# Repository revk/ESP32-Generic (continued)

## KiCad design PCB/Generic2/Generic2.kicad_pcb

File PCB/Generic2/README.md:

# Generic2

## Trademark

This is an open source project, but bear in mind you cannot sell boards bearing the Andrews & Arnold Ltd name, the A&A logo, the registered trademark AJK logo, or the GS1 allocated EANs assigned to Andrews & Arnold Ltd.

## PCB Designs

These files are for use with [KiCAD](https://www.kicad.org).

- [Generic2](Generic2.kicad_pro)
## 3D

3D case designs are normally automatically created from the PCB so as to ensure correct details and placement of apertures, etc.

- [Generic2](Generic2.stl)

## Images

---

*Auto generated README.md 2025-08-25T14:29:06*

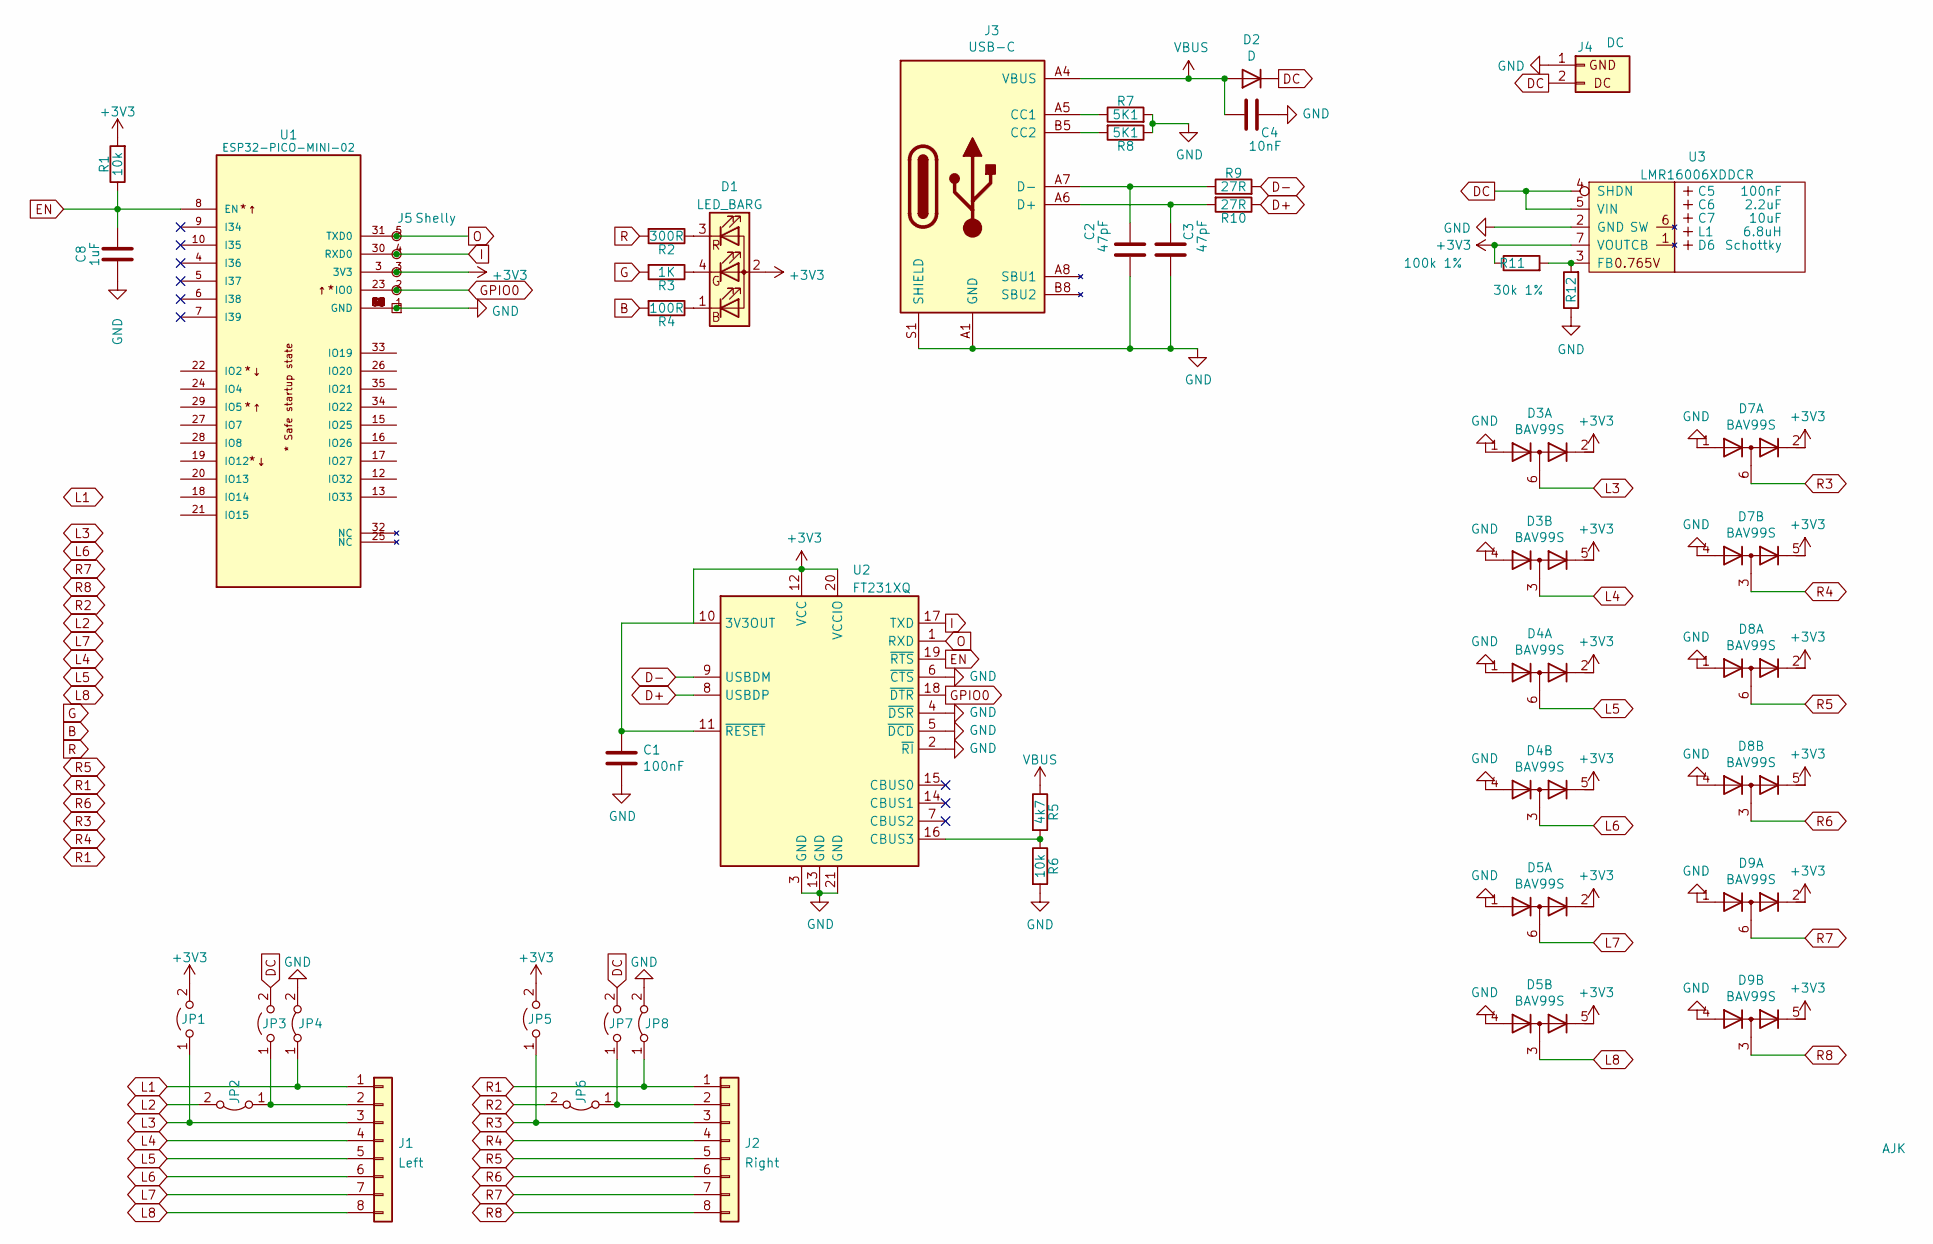
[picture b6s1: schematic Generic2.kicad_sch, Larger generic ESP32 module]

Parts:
C1: 100nF; C_0603
C2, C3: 47pF; C_0603
C4: 10nF; C_0603
C5: 100nF; C_0603_; MPN C30926
C6: 2.2uF; C_0805_; MPN C19110
C7: 10uF; C_0805_; MPN C17024
C8: 1uF; C_0603
D1: LED_BARG; MHS190RGBCT; MPN C409798
D2: D; D_1206_3216Metric
D3, D4, D5, D7, D8, D9: BAV99S; SOT-363_SC-70-6; Part No BAV99S
D6: Schottky; D_1206_; MPN C143805
J1: Left; PTSM-HH-8-RA
J2: Right; PTSM-HH-8-RA
J3: USB-C; USC16-TR; Part No CSP-USC16-TR
J4: DC
J5: Shelly
JP1, JP5: L3; Pad_1206_0805_Open
JP2, JP6: L2; Pad_1206_0805_Bridged
JP3, JP7: L2; Pad_1206_0805_Open
JP4, JP8: L1; Pad_1206_0805_Bridged
L1: 6.8uH; L_4x4_; MPN C354575
Logo1: AJK
R1, R6: 10k; R_0603
R2: 300R; R_0603; Part No 0603-680R
R3: 1K; R_0603; Part No 0603-2K
R4: 100R; R_0603; Part No 0603-220R
R5: 4k7; R_0603
R7, R8: 5K1; R_0603
R9, R10: 27R; R_0603
R11: 100k 1%; R_0603; MPN C14675
R12: 30k 1%; R_0603; MPN C100001
U1: ESP32-PICO-MINI-02; PARTREV v1.0
U2: FT231XQ; QFN-20-1EP_4x4mm_P0.5mm_EP2.5x2.5mm
U3: LMR16006XDDCR; SOT-23-Thin-6-Reg; Part No LMR16006XDDCR

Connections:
+3V3: C1.1, D1.2 (A), D3.2 (K2), D3.5 (K4), D4.2 (K2), D4.5 (K4), D5.2 (K2), D5.5 (K4), D7.2 (K2), D7.5 (K4), D8.2 (K2), D8.5 (K4), D9.2 (K2), D9.5 (K4), J5.3 (3V3), JP1.2 (B), JP5.2 (B), R1.2, R11.1, U1.3 (3V3), U2.10 (3V3OUT), U2.11 (~RESET), U2.12 (VCC), U2.20 (VCCIO), U3.7 (VOUT)
B: R4.2
D+: R10.1, U2.8 (USBDP)
D-: R9.2, U2.9 (USBDM)
DC: D2.1 (K), J4.2 (DC), JP3.2 (B), JP7.2 (B), U3.4 (SHDN), U3.5 (VIN)
EN: C8.2, R1.1, U1.8 (EN), U2.19 (~RTS)
G: R3.2
GND: C1.2, C2.2, C3.2, C4.1, C8.1, D3.1 (A1), D3.4 (A3), D4.1 (A1), D4.4 (A3), D5.1 (A1), D5.4 (A3), D7.1 (A1), D7.4 (A3), D8.1 (A1), D8.4 (A3), D9.1 (A1), D9.4 (A3), J3.A1 (GND), J3.A12 (GND), J3.B1 (GND), J3.B12 (GND), J3.S1 (SHIELD), J4.1 (GND), J5.1 (GND), JP4.2 (B), JP8.2 (B), R6.2, R7.2, R8.1, R12.1, U1.1 (GND), U1.2 (GND), U1.11 (GND), U1.14 (GND), U1.36 (GND), U1.37 (GND), U1.38 (GND), U1.39 (GND), U1.40 (GND), U1.41 (GND), U1.42 (GND), U1.43 (GND), U1.44 (GND), U1.45 (GND), U1.46 (GND), U1.47 (GND), U1.48 (GND), U1.49 (GND), U1.50 (GND), U1.51 (GND), U1.52 (GND), U1.53 (GND), U2.2 (~RI), U2.3 (GND), U2.4 (~DSR), U2.5 (~DCD), U2.6 (~CTS), U2.13 (GND), U2.21 (GND), U3.2 (GND)
GPIO0: J5.2 (0), U1.23 (IO0), U2.18 (~DTR)
I: J5.4 (Rx), U1.30 (RXD0), U2.17 (TXD)
L1: J1.1, JP4.1 (A)
L2: JP2.2 (B)
L3: D3.6 (K3A4), J1.3, JP1.1 (A)
L4: D3.3 (K1A2), J1.4
L5: D4.6 (K3A4), J1.5
L6: D4.3 (K1A2), J1.6
L7: D5.6 (K3A4), J1.7
L8: D5.3 (K1A2), J1.8
unnamed: C2.1, J3.A7 (D-), J3.B7 (D-), R9.1
unnamed: C3.1, J3.A6 (D+), J3.B6 (D+), R10.2
unnamed: D1.1 (BK), R4.1
unnamed: D1.4 (GK), R3.1
unnamed: D1.3 (RK), R2.1
unnamed: J1.2, JP2.1 (A), JP3.1 (A)
unnamed: J2.2, JP6.1 (A), JP7.1 (A)
unnamed: J3.A5 (CC1), R7.1
unnamed: J3.B5 (CC2), R8.2
unnamed: R5.2, R6.1, U2.16 (CBUS3)
unnamed: R11.2, R12.2, U3.3 (FB)
O: J5.5 (Tx), U1.31 (TXD0), U2.1 (RXD)
R: R2.2
R1: J2.1, JP8.1 (A)
R2: JP6.2 (B)
R3: D7.6 (K3A4), J2.3, JP5.1 (A)
R4: D7.3 (K1A2), J2.4
R5: D8.6 (K3A4), J2.5
R6: D8.3 (K1A2), J2.6
R7: D9.6 (K3A4), J2.7
R8: D9.3 (K1A2), J2.8
VBUS: C4.2, D2.2 (A), J3.A4 (VBUS), J3.A9 (VBUS), J3.B4 (VBUS), J3.B9 (VBUS), R5.1

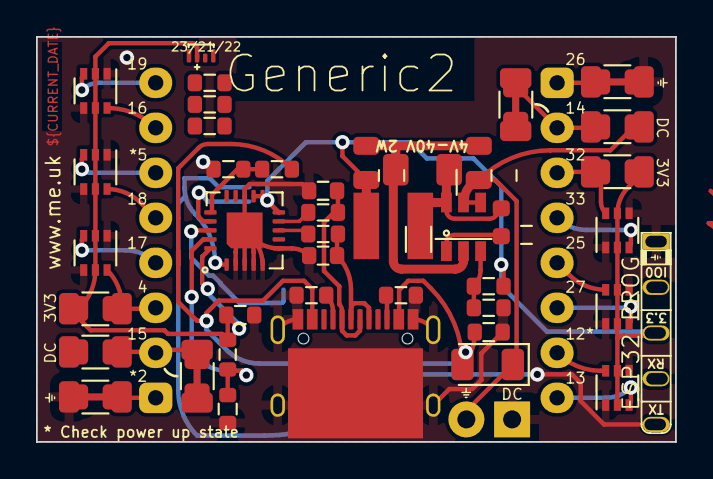
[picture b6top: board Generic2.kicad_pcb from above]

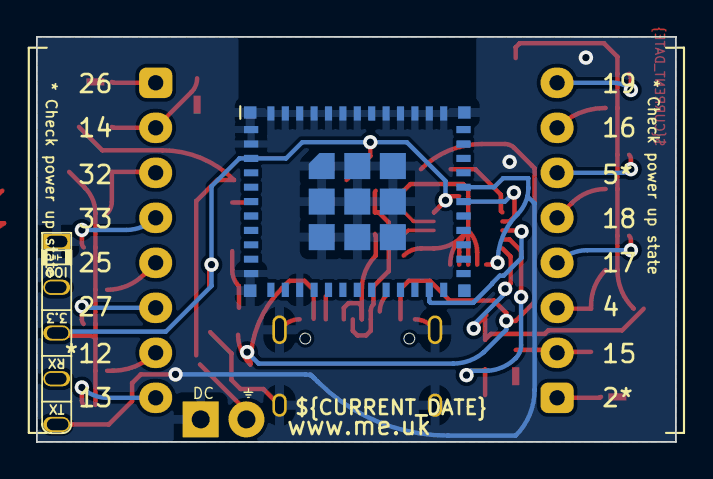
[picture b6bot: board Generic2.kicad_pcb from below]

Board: 2 copper layers, 35.5 x 22.5 mm, 47 parts (4 on the bottom side), 35 nets.

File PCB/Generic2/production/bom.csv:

Designator,Footprint,Quantity,Value,LCSC Part #
C1,C_0603,1,100nF,
"C2, C3",C_0603,2,47pF,
C4,C_0603,1,10nF,
C5,C_0603_,1,100nF,C30926
C6,C_0805_,1,2.2uF,C19110
C7,C_0805_,1,10uF,C17024
D1,MHS190RGBCT,1,LED_BARG,C409798
D2,1206,1,D,
"D3, D4, D5, D7, D8, D9",SOT-363_SC-70-6,6,BAV99S,
D6,D_1206_,1,Schottky,C143805
J1,PTSM-HH-8-RA,1,Left,
J2,PTSM-HH-8-RA,1,Right,
J3,USC16-TR,1,USB-C,
L1,L_4x4_,1,6.8uH,C354575
"R1, R6",R_0603,2,10k,
"R10, R9",R_0603,2,27R,
R11,R_0603,1,100k 1%,C14675
R12,R_0603,1,30k 1%,C100001
R2,R_0603,1,300R,
R3,R_0603,1,1K,
R4,R_0603,1,100R,
R5,R_0603,1,4k7,
"R7, R8",R_0603,2,5K1,
U1,ESP32-WROOM-32,1,ESP32-WROOM-32,
U2,QFN-20-1EP_4x4mm_P0.5mm_EP2.5x2.5mm,1,FT231XQ,
U3,SOT-23-Thin-6-Reg,1,LMR16006XDDCR,C87080

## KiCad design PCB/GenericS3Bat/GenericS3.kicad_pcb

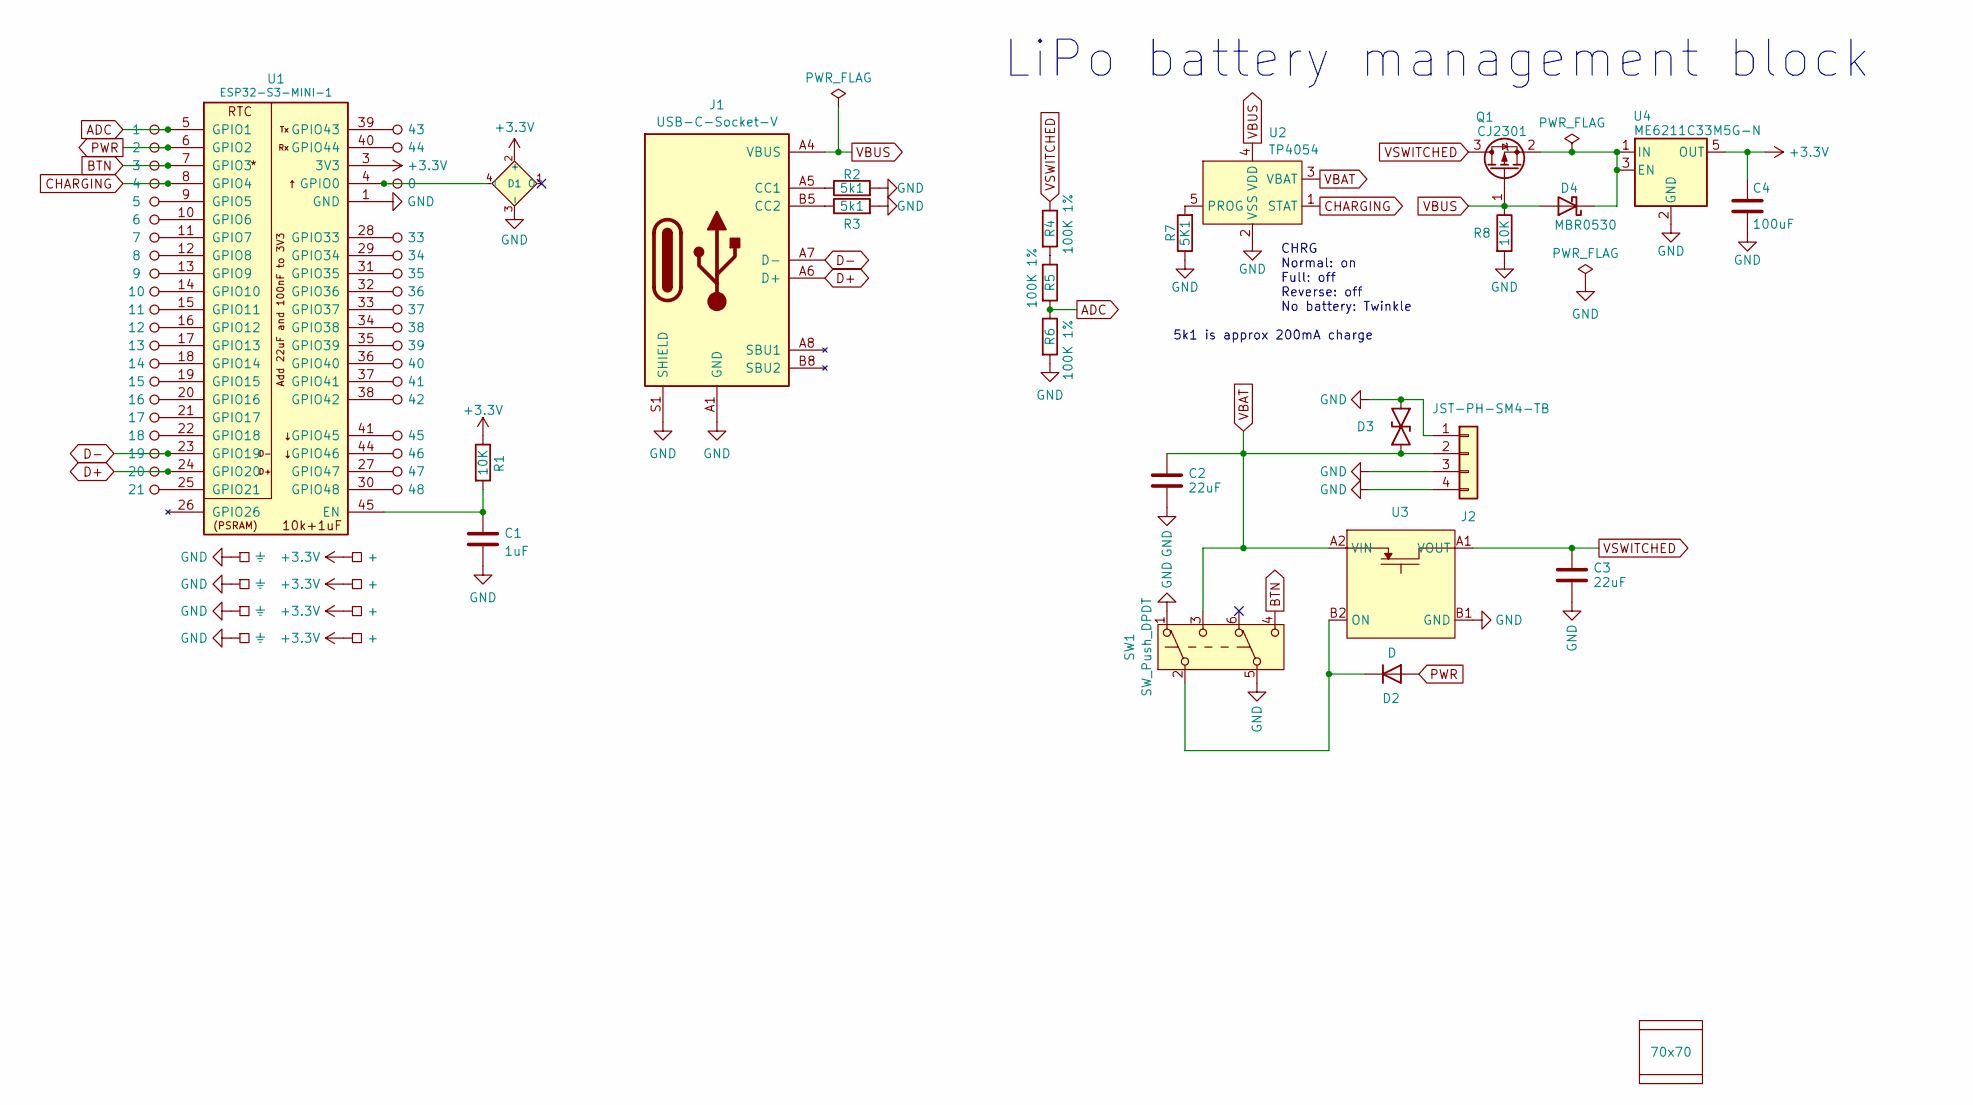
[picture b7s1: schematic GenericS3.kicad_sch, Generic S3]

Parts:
C1: 1uF; C_0201
C2, C3: 22uF; C_0603
C4: 100uF; C_0805; MPN C141660
D1: XL-1010RGBC-WS2812B; SMD1010-Side2; MPN C5349953
D2: D; D_0402; MPN C28642302
D3: DFN1006-2L; MPN C5137770
D4: MBR0530; D_SOD-123; MPN C5204746
J1: USB-C-Socket-V; USB-C-Socket-H; MPN C709357
J2: JST-PH-SM4-TB; JST_PH_S2B-PH-SM4-TB_1x02-1MP_P2.00mm_Horizontal; MPN C295747
P1: 33; Round
P2: 34; Round
P3: 35; Round
P4: 36; Round
P5: 37; Round
P6: 38; Round
P7: 39; Round
P8: 40; Round
P9: 41; Round
P10: 42; Round
P11: 45; Round
P12: 46; Round
P13: 47; Round
P14: 48; Round
P15: 18; Round
P16: 19; Round
P17: 14; Round
P18: 15; Round
P19: 16; Round
P20: 17; Round
P21: 6; Round
P22: 7; Round
P23: 8; Round
P24: 9; Round
P25: 20; Round
P26: 10; Round
P27: 11; Round
P28: 12; Round
P29: 13; Round
P30: 1; Round
P31: 2; Round
P32: 3; Round
P33: 4; Round
P34: 5; Round
P35: 21; Round
P36: 43; Round
P37: 44; Round
P38: 0; Round
P39, P40, P41, P42: ⏚; Square
P43, P44, P45, P46: +; Square
PCB1: 70x70; PCB7070
Q1: CJ2301; SOT-23; MPN C8547
R1: 10K; R_0201; MPN C106225
R2, R3: 5k1; R_0201; MPN C274341
R4, R5, R6: 100K 1%; R_0201
R7: 5K1; R_0201
R8: 10K; R_0201
SW1: SW_Push_DPDT; MPN C2911139
U1: ESP32-S3-MINI-1; MPN C3013941
U2: TP4054; SOT-23-5; MPN C668215
U3: WCSP-4-0.78x0.78; MPN C2655476
U4: ME6211C33M5G-N; SOT-23-5; MPN C82942
V1, V2: 70; VCUT70

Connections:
+3.3V: C4.1, D1.2 (+), P43.1, P44.1, P45.1, P46.1, R1.1, U1.3 (3V3), U4.5 (OUT)
ADC: P30.1, R5.2, R6.1, U1.5 (GPIO1)
BTN: P32.1, SW1.4 (C), U1.7 (GPIO3)
CHARGING: P33.1, U1.8 (GPIO4), U2.1 (STAT)
D+: J1.A6 (D+), J1.B6 (D+), P25.1, U1.24 (GPIO20)
D-: J1.A7 (D-), J1.B7 (D-), P16.1, U1.23 (GPIO19)
GND: C1.2, C2.2, C3.2, C4.2, D1.3 (-), D3.1, J1.A1 (GND), J1.A12 (GND), J1.B1 (GND), J1.B12 (GND), J1.S1 (SHIELD), J2.1, J2.3, J2.4, P39.1, P40.1, P41.1, P42.1, R2.2, R3.2, R6.2, R7.1, R8.2, SW1.1 (A), SW1.5 (B), U1.1 (GND), U1.2 (GND), U1.42 (GND), U1.43 (GND), U1.46 (GND), U1.47 (GND), U1.48 (GND), U1.49 (GND), U1.50 (GND), U1.51 (GND), U1.52 (GND), U1.53 (GND), U1.54 (GND), U1.55 (GND), U1.56 (GND), U1.57 (GND), U1.58 (GND), U1.59 (GND), U1.60 (GND), U1.61 (GND), U1.62 (GND), U1.63 (GND), U1.64 (GND), U1.65 (GND), U2.2 (VSS), U3.B1 (GND), U4.2 (GND)
unnamed: D1.4 (I), P38.1, U1.4 (GPIO0)
unnamed: D2.1 (K), SW1.2 (B), U3.B2 (ON)
unnamed: D4.1 (K), Q1.2 (S), U4.1 (IN), U4.3 (EN)
unnamed: J1.A5 (CC1), R2.1
unnamed: J1.B5 (CC2), R3.1
unnamed: P1.1, U1.28 (GPIO33)
unnamed: P2.1, U1.29 (GPIO34)
unnamed: P3.1, U1.31 (GPIO35)
unnamed: P4.1, U1.32 (GPIO36)
unnamed: P5.1, U1.33 (GPIO37)
unnamed: P6.1, U1.34 (GPIO38)
unnamed: P7.1, U1.35 (GPIO39)
unnamed: P8.1, U1.36 (GPIO40)
unnamed: P9.1, U1.37 (GPIO41)
unnamed: P10.1, U1.38 (GPIO42)
unnamed: P11.1, U1.41 (GPIO45)
unnamed: P12.1, U1.44 (GPIO46)
unnamed: P13.1, U1.27 (GPIO47)
unnamed: P14.1, U1.30 (GPIO48)
unnamed: P15.1, U1.22 (GPIO18)
unnamed: P17.1, U1.18 (GPIO14)
unnamed: P18.1, U1.19 (GPIO15)
unnamed: P19.1, U1.20 (GPIO16)
unnamed: P20.1, U1.21 (GPIO17)
unnamed: P21.1, U1.10 (GPIO6)
unnamed: P22.1, U1.11 (GPIO7)
unnamed: P23.1, U1.12 (GPIO8)
unnamed: P24.1, U1.13 (GPIO9)
unnamed: P26.1, U1.14 (GPIO10)
unnamed: P27.1, U1.15 (GPIO11)
unnamed: P28.1, U1.16 (GPIO12)
unnamed: P29.1, U1.17 (GPIO13)
unnamed: P34.1, U1.9 (GPIO5)
unnamed: P35.1, U1.25 (GPIO21)
unnamed: P36.1, U1.39 (GPIO43)
unnamed: P37.1, U1.40 (GPIO44)
unnamed: R4.2, R5.1
unnamed: C1.1, R1.2, U1.45 (EN)
unnamed: R7.2, U2.5 (PROG)
PWR: D2.2 (A), P31.1, U1.6 (GPIO2)
VBAT: C2.1, D3.2, J2.2, SW1.3 (C), U2.3 (VBAT), U3.A2 (VIN)
VBUS: D4.2 (A), J1.A4 (VBUS), J1.A9 (VBUS), J1.B4 (VBUS), J1.B9 (VBUS), Q1.1 (G), R8.1, U2.4 (VDD)
VSWITCHED: C3.1, Q1.3 (D), R4.1, U3.A1 (VOUT)

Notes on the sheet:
5k1 is approx 200mA charge
CHRG Normal: on Full: off Reverse: off No battery: Twinkle
LiPo battery management block

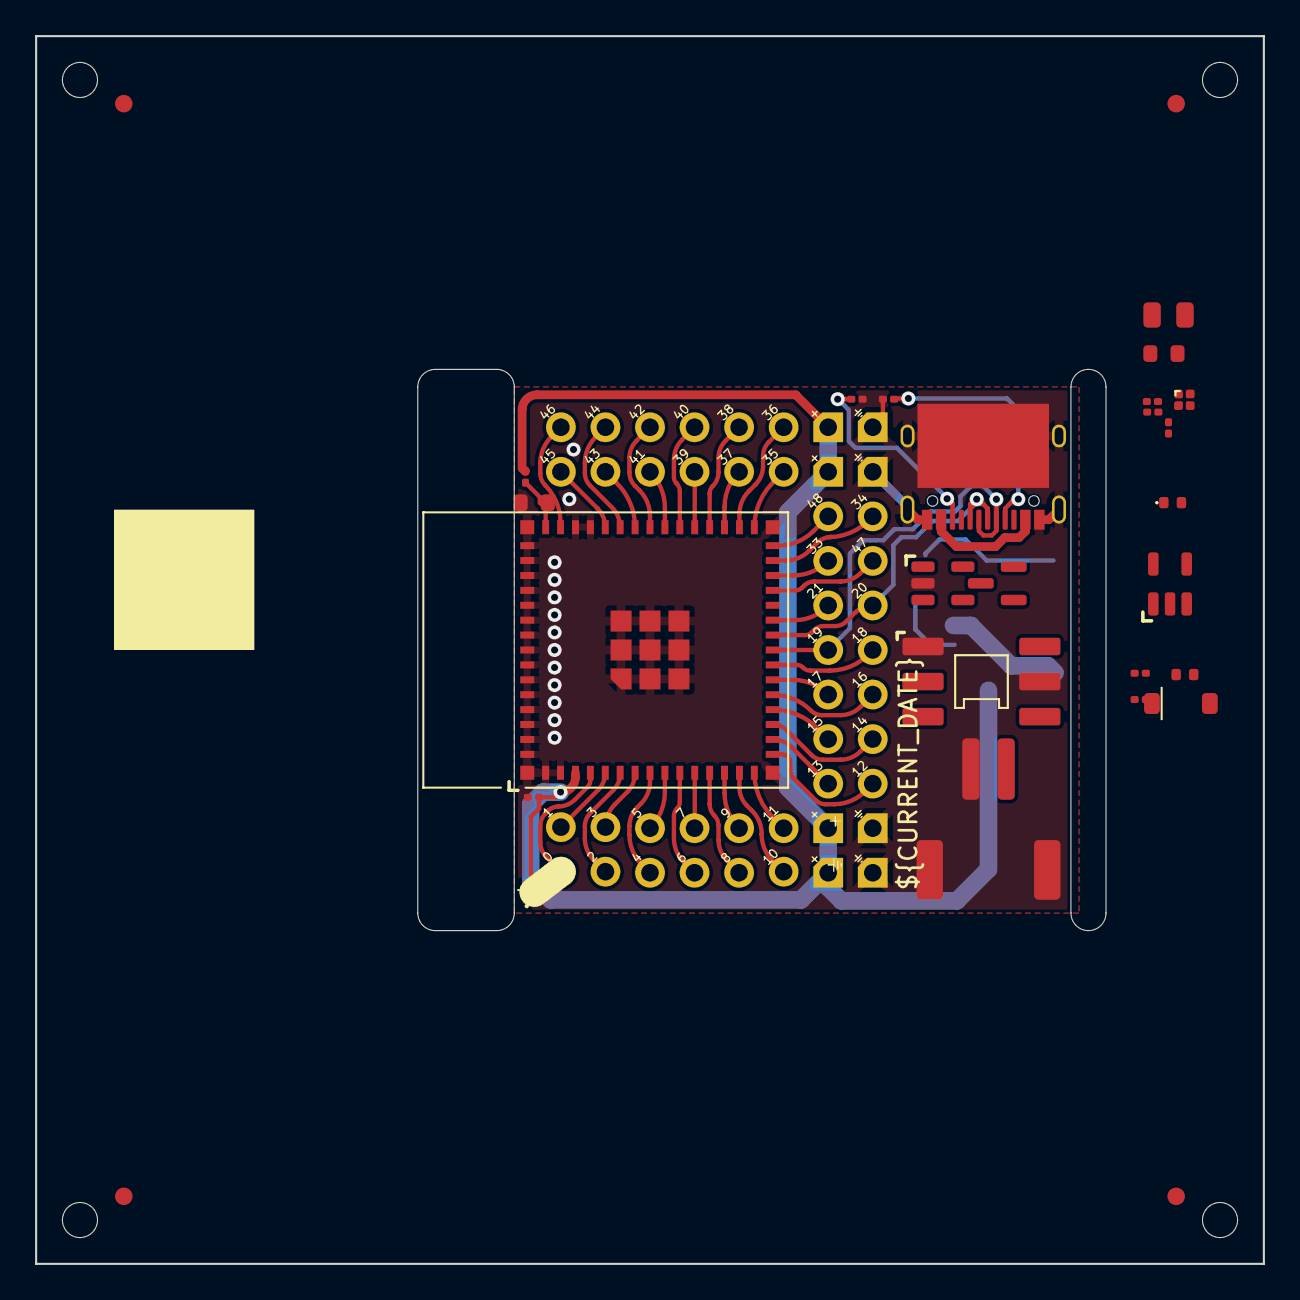
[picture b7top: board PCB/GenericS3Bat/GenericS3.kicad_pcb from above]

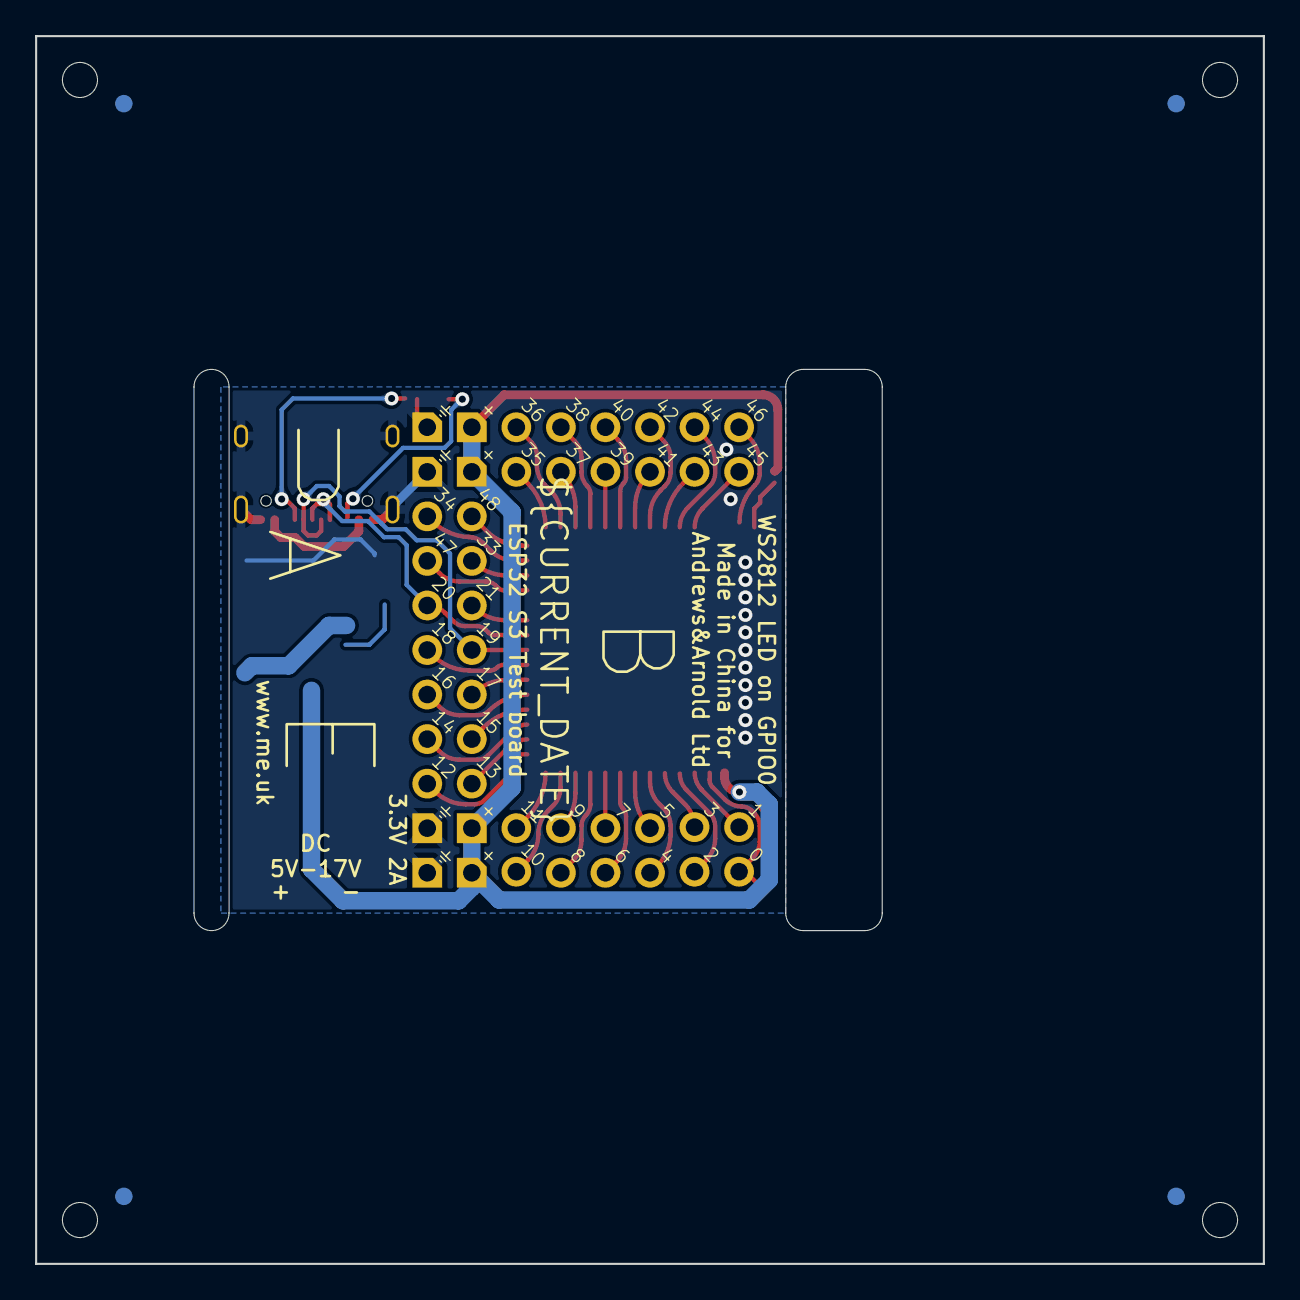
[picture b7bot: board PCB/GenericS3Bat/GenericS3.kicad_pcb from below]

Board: 2 copper layers, 70.0 x 70.0 mm, 73 parts (2 on the bottom side), 50 nets.

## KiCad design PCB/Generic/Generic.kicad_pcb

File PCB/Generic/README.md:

# Generic

These files are for use in [KiCad](https://www.kicad.org).

## Trademark

This is an open source project, but bear in mind you cannot sell boards bearing the Andrews & Arnold Ltd name, the A&A logo, the registered trademark AJK logo, or the GS1 allocated EANs assigned to Andrews & Arnold Ltd.

## Images

*Auto generated 2025-08-24T13:25:42*

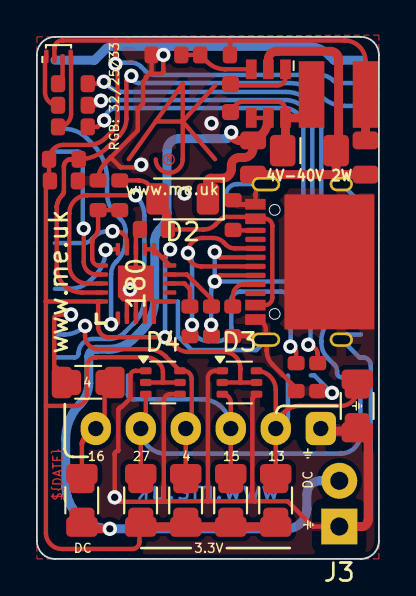
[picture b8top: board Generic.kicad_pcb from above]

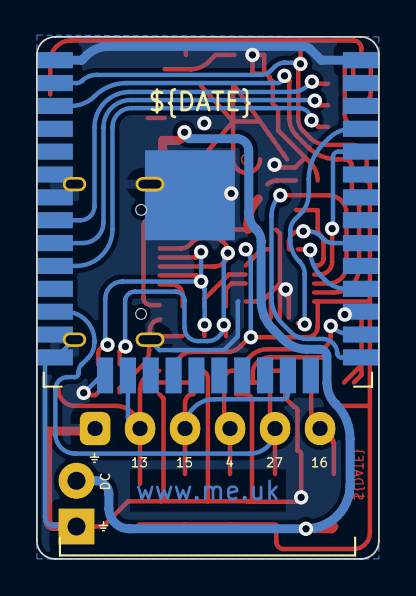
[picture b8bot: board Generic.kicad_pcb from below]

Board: 2 copper layers, 19.0 x 29.0 mm, 39 parts (2 on the bottom side), 28 nets.

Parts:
C1: NF; Pad_1206_0805_Open
C2: 100nF; C_0603
C3, C4: 47pF; C_0603
C5: 10nF; C_0603
C6: 100nF; C_0603_
C7: 2.2uF; C_0805_
C8: 10uF; C_0805_
D1: LED_BARG; MHS190RGBCT
D2: D; D_1206_3216Metric
D3, D4: BAV99S; SOT-363_SC-70-6
D5: Schottky; D_1206_
J1: Connector; PTSM-HH-6-RA
J2: USB-C; USC16-TR
J3: DC
L1: 6.8uH; L_4x4_
Logo1: AJK
R1, R16: 10k; R_0603
R2, R3, R4, R5, R6, R7: NF; Pad_1206_0805_Open
R8: 300R; R_0603
R9: 1K; R_0603
R10: 100R; R_0603
R11, R12: 5K1; R_0603
R13, R14: 27R; R_0603
R15: 4k7; R_0603
R17: 100k 1%; R_0603
R18: 30k 1%; R_0603
U1: ESP32-WROOM-32
U2: FT231XQ; QFN-20-1EP_4x4mm_P0.5mm_EP2.5x2.5mm
U3: LMR16006XDDCR; SOT-23-Thin-6-Reg

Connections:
+3V3: C2.1, D1.2 (A), D3.2 (K2), D3.5 (K4), D4.2 (K2), D4.5 (K4), R1.2, R2.1, R3.1, R4.1, R5.1, R17.1, U1.2 (VDD), U2.10 (3V3OUT), U2.11 (~RESET), U2.12 (VCC), U2.20 (VCCIO), U3.7 (VOUT)
B: R10.2, U1.9 (IO33)
CHARGER: U1.30 (IO18), U2.14 (CBUS1)
D+: R14.1, U2.8 (USBDP)
D-: R13.2, U2.9 (USBDM)
DC: D2.1 (K), J3.2 (DC), R6.1, U3.4 (SHDN), U3.5 (VIN)
EN: R1.1, U1.3 (EN), U2.19 (~RTS)
G: R9.2, U1.10 (IO25)
GND: C1.1, C2.2, C3.2, C4.2, C5.1, D3.1 (A1), D3.4 (A3), D4.1 (A1), D4.4 (A3), J1.1, J2.A1 (GND), J2.A12 (GND), J2.B1 (GND), J2.B12 (GND), J2.S1 (SHIELD), J3.1 (GND), R11.2, R12.1, R16.2, R18.1, U1.1 (GND), U1.6 (IO34), U1.7 (IO35), U1.13 (IO14), U1.14 (IO12), U1.15 (GND), U1.38 (GND), U1.39 (GND), U2.2 (~RI), U2.3 (GND), U2.4 (~DSR), U2.5 (~DCD), U2.6 (~CTS), U2.13 (GND), U2.21 (GND), U3.2 (GND)
GPIO0: U1.25 (IO0), U2.18 (~DTR)
I: U1.34 (RXD0/IO3), U2.17 (TXD)
IO1: C1.2, D3.6 (K3A4), J1.2, R2.2, U1.16 (IO13)
IO2: D3.3 (K1A2), J1.3, R3.2, U1.23 (IO15)
IO3: D4.6 (K3A4), J1.4, R4.2, U1.26 (IO4)
IO4: D4.3 (K1A2), J1.5, R5.2, U1.12 (IO27)
IO5: R7.1, U1.27 (IO16)
unnamed: C3.1, J2.A7 (D-), J2.B7 (D-), R13.1
unnamed: C4.1, J2.A6 (D+), J2.B6 (D+), R14.2
unnamed: D1.1 (BK), R10.1
unnamed: D1.3 (RK), R8.1
unnamed: D1.4 (GK), R9.1
unnamed: R6.2, R7.2
unnamed: R15.2, R16.1
unnamed: R17.2, R18.2
O: U1.35 (TXD0/IO1), U2.1 (RXD)
R: R8.2, U1.8 (IO32)
USB: U1.28 (IO17), U2.15 (CBUS0)
VBUS: C5.2, D2.2 (A), J2.A4 (VBUS), J2.A9 (VBUS), J2.B4 (VBUS), J2.B9 (VBUS), R15.1

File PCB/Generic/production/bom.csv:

Designator,Footprint,Quantity,Value,LCSC Part #
C2,C_0603,1,100nF,
"C3, C4",C_0603,2,47pF,
C5,C_0603,1,10nF,
C6,C_0603_,1,100nF,C30926
C7,C_0805_,1,2.2uF,C19110
C8,C_0805_,1,10uF,C17024
D1,MHS190RGBCT,1,LED_BARG,C409798
D2,1206,1,D,
"D3, D4",SOT-363_SC-70-6,2,BAV99S,
D5,D_1206_,1,Schottky,C143805
J1,PTSM-HH-6-RA,1,Connector,
J2,USC16-TR,1,USB-C,
L1,L_4x4_,1,6.8uH,C354575
"R1, R16",R_0603,2,10k,
R10,R_0603,1,100R,
"R11, R12",R_0603,2,5K1,
"R13, R14",R_0603,2,27R,
R15,R_0603,1,4k7,
R17,R_0603,1,100k 1%,C14675
R18,R_0603,1,30k 1%,C100001
R8,R_0603,1,300R,
R9,R_0603,1,1K,
U1,ESP32-WROOM-32,1,ESP32-WROOM-32,
U2,QFN-20-1EP_4x4mm_P0.5mm_EP2.5x2.5mm,1,FT231XQ,
U3,SOT-23-Thin-6-Reg,1,LMR16006XDDCR,C87080

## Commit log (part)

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2022-03-17 Library update
2022-03-17 Message
2022-03-17 New displays
2022-03-18 New suffixes
2022-03-18 Try that
2022-03-29 Changed to have C/R for EN
2022-04-02 Debug for daikin
2022-04-03 S21 Daikin debug
2022-04-03 S21 debug
2022-04-04 Extra tiny board with optional components. Smallest yet
2022-04-04 Tidy Generic 4 Started on Generic 6
2022-04-06 Update manual
2022-04-06 http
2022-04-06 Linked in
2022-04-07 WiFi
2022-04-09 Tidy
2022-04-18 Direct solaredge API for monitoring
2022-04-18 Use jo_find
2022-04-18 Unicode
2022-04-18 Changed jo_find
2022-04-18 Today usage
2022-04-18 City
2022-04-18 Lines
2022-04-18 Log today
2022-04-18 More data logged
2022-04-18 More
2022-04-18 More detail
2022-04-19 Wh and W when <1000
2022-04-27 Non display
2022-04-27 Tweak
2022-05-01 New Generic board 6
2022-05-01 Generic 6 not finished
2022-05-02 Generic 6 tracked
2022-05-03 Curvy tracks
2022-05-19 DEFCON feature ;-)
2022-05-19 Tweak - blink done on output task now
2022-05-20 Direct DEFCON/n command
2022-05-22 Tidy defaults
2022-05-26 Playing with web interface for DEFCON
2022-05-28 Tweak icon
2022-05-28 DEFCON web
2022-05-28 Add wifi link
2022-05-28 More defcon modes
2022-05-29 A few more options
2022-06-09 Inputs (with pull down and up)
2022-06-21 Tweak sdkconfig
2022-12-31 More v5.0
2023-01-03 USB plug generic
2023-01-05 PCB make
2023-01-05 PCB zip file in Make
2023-01-05 Missed on
2023-01-05 Improved zip make
2023-01-05 Latest and zips
2023-01-09 Moved PCB directory
2023-01-09 Cases
2023-02-10 New layout for production
2023-02-17 Started a variation
2023-02-17 Right angle version
2023-03-18 New layoput
2023-03-19 Colour
2023-03-29 Details
2023-03-29 Right images
2023-03-29 Readme
2023-03-29 typo
2023-04-06 More tidy
2023-04-07 New LED Generic 5
2023-04-07 New PCB
2023-04-08 Moved PCB
2023-06-14 Production files
2023-06-14 Move RST
2023-06-14 Tidy RST as EN
2023-06-17 Silk
2023-06-17 Started some updates, not all complete
2023-06-17 Messing around, not good
2023-06-20 Simple USBA with CH340X
2023-06-20 Smaller footprint on CH340X
2023-06-21 Rotation fixes
2023-06-24 New regulator
2023-06-25 Smaller
2023-06-25 Panel
2023-06-25 Extra silk screen
2023-06-26 Re panel
2023-06-26 Logo
2023-06-26 Tear drops
2023-06-26 FFS missing 4k7
2023-06-26 V Cuts
2023-06-27 Better rails
2023-06-27 Fix CH340X
2023-06-29 Move UART, and tidy
2023-06-30 Added H.T
2023-06-30 Order
2023-07-02 Bodged back to compiling
2023-07-07 Wow, stack does not work!
2023-07-13 Swapped around a bit
2023-07-20 Started rework for single sided
2023-07-20 New layout
2023-07-20 Needs tracks tidying
2023-07-20 Cleaner tracks
2023-07-27 1mm with glued bits
2023-07-30 As ordered
2023-08-01 New ESP32-S3 based module
2023-08-01 Fix cuts
2023-08-01 Tidy, fix GND, and add tear drops
2023-08-01 Test board
2023-08-02 Added GND pads
2023-08-04 Added connector
2023-08-04 Cut out
2023-08-04 Diode
2023-08-04 Remove socket from BOM
2023-08-04 ESD symbol on silk
2023-08-04 Added 3V3 pads as well
2023-08-05 Changed diode
2023-08-05 Fix diode and barcode
2023-08-06 PROG under ESP
2023-08-07 Not quite ready for ESP32S3 yet
2023-08-08 Added buttons
2023-08-09 USBA as latest, and improve silk screen
2023-08-09 text
2023-08-09 Smaller footprint
2023-08-09 Ordered smaller
2023-08-10 No buttons
2023-08-10 Packed in to 30x30mm
2023-08-10 Smaller diode
2023-08-11 No barcode
2023-08-11 Adding DS18B20
2023-08-11 DS18B20
2023-08-11 Format
2023-08-18 Tidy up silk screen for glue on tab
2023-08-18 New images
2023-08-19 New reg
2023-08-29 Tidy and new artwork on USBA
2023-08-29 Added USB pads to allow programming in panel
2023-09-05 Changed to WS2812
2023-09-28 Slight angle fixed
2023-10-10 Changed to light sensor
2023-10-19 Added 3 pads for LED
2023-10-28 USB-C version
2023-10-28 Better layout
2023-10-28 Remove EAN for now
2023-10-28 Note
2023-10-28 Reworked, double sided (meh), and more LEDs
2023-10-28 More caps
2023-10-28 Tidy for production
2023-10-28 Tidy for prod
2023-10-28 Update README.md
    New pics
2023-10-28 Update README.md
    Description
2023-10-28 Update README.md
    Pics
2023-10-28 Update README.md
    Fixed pics
2023-10-28 Update README.md
    Button
2023-10-28 Tidy tracks
2023-10-28 Added simple GPIO0 LED
2023-10-28 Labeled 0
2023-11-04 FFS - different CC logic for a plug
2023-11-05 More solid plug
2023-11-05 Fix CC
2023-11-11 Adjusted
2023-11-15 More testing
2024-08-11 Tweak layout
2024-08-20 Tweak layout for WAGO on back
2024-08-20 Re do GPIO
2024-08-20 Put back I2C device
2024-08-21 New design, 3 pin WAGO for LED, I2S microphone, and colour sensor.
2024-08-25 Tidy mic
2024-08-26 Clean up
2024-08-26 New EAN
2024-08-27 Tidy tab and add extra cap and ESD
2024-09-02 Tweak wago placement
2024-09-03 Moved to LED
2025-01-23 PCB Update
2025-07-02 New renders and new S3
2025-07-02 Render adjust
2025-07-03 ready to order
2025-07-04 Re-jiggered
2025-07-05 Tidy up a bit
2025-07-09 New render
2025-07-09 Re render
2025-07-10 Reference battery started
2025-07-11 Added diode
2025-07-17 Change reg
2025-07-19 Re build
2025-07-19 led strip
2025-07-19 Started on LoRA
2025-07-19 Tx is not sending, grrr
2025-07-20 Started logic - need to rework LoRa code
2025-07-23 LCD2
2025-07-24 Latest tweaks
2025-07-24 More caps, and change to ceramic
2025-07-24 3A diodes
2025-07-25 Beta
2025-07-26 Tweak layout a bit
2025-07-26 Re-render
2025-08-24 Renders
2025-08-25 New case
2025-08-25 Improved README
2025-08-25 Datecode
2025-10-10 new LEDs
2025-11-13 Actuator logic and new LEDs
2025-11-13 Web actuation
2026-02-13 submodule
2026-02-15 Codeberg
